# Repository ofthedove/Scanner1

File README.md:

# Scanner1
Simple LED scanner with two buttons controlled by an ATmega32U4

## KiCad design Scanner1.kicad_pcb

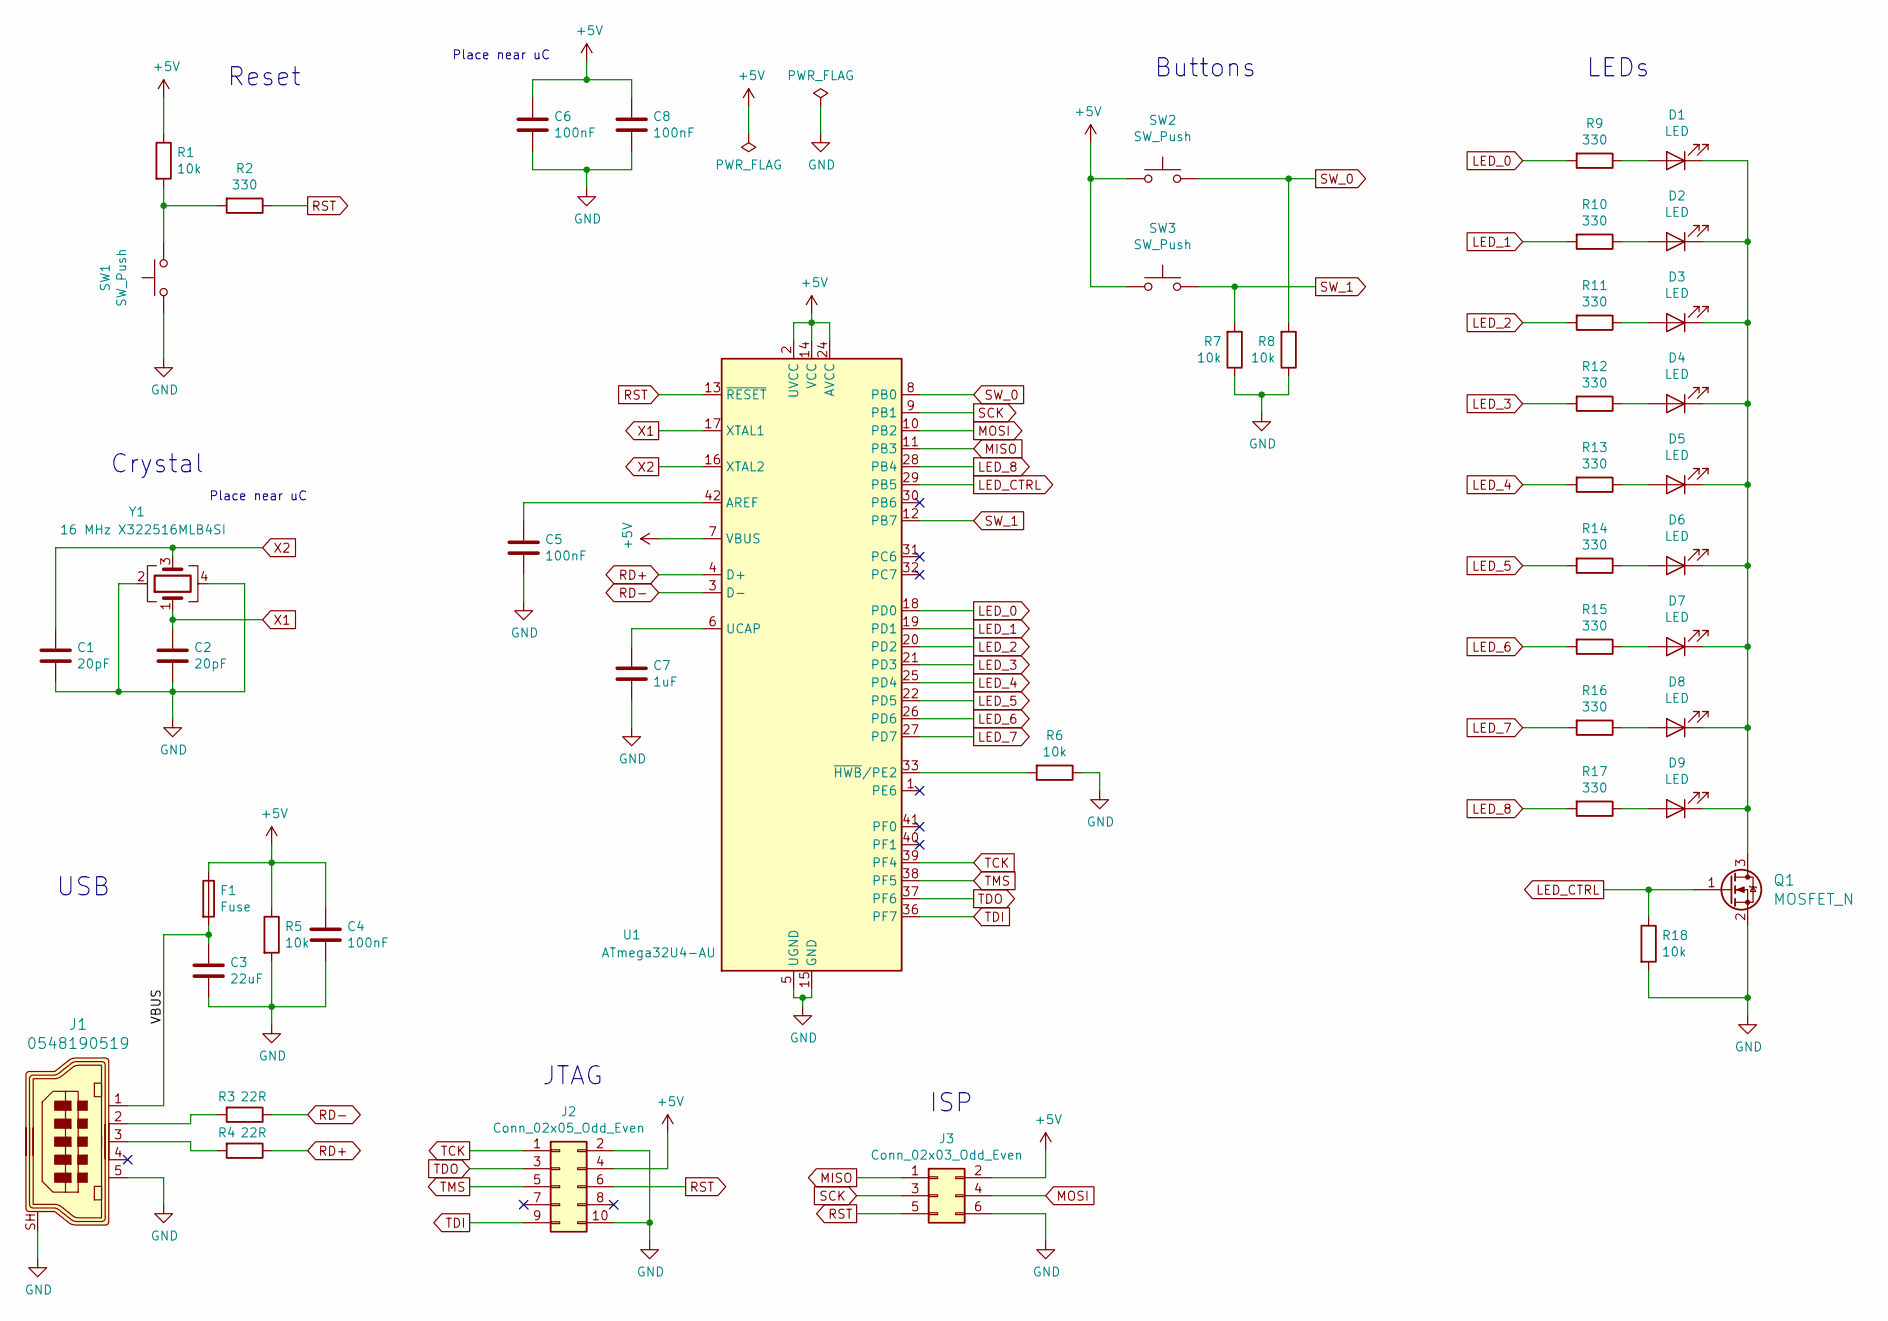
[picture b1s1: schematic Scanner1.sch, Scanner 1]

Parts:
C1, C2: 20pF; C_0805_2012Metric; LCSC Part # C1798
C3: 22uF; C_0805_2012Metric; LCSC Part # C45783
C4, C5, C6, C8: 100nF; C_0805_2012Metric; LCSC Part # C49678
C7: 1uF; C_0805_2012Metric; LCSC Part # C28323
D1, D2, D3, D4, D5, D6, D7, D8, D9: LED; LED_0805_2012Metric; LCSC Part # C2293
F1: Fuse; Fuse_0805_2012Metric; LCSC Part # C116170
J1: 0548190519; USB_Mini_B_Female_548190519; MPN 0548190519; Digi-Key_PN WM17115-ND
J2: Conn_02x05_Odd_Even; PinHeader_2x05_P2.54mm_Vertical
J3: Conn_02x03_Odd_Even; PinHeader_2x03_P2.54mm_Vertical
Q1: MOSFET_N; SOT-23; LCSC Part # C20917
R1, R5, R6, R7, R8, R18: 10k; R_0805_2012Metric; LCSC Part # C17414
R2, R9, R10, R11, R12, R13, R14, R15, R16, R17: 330; R_0805_2012Metric; LCSC Part # C17630
R3, R4: 22R; R_0805_2012Metric; LCSC Part # C17561
SW1, SW2, SW3: SW_Push; SW_PUSH_6mm_H7.3mm
U1: ATmega32U4-AU; TQFP-44_10x10mm_P0.8mm; LCSC Part # C44854
Y1: 16 MHz X322516MLB4SI; Crystal_SMD_3225-4Pin_3.2x2.5mm; LCSC Part # C13738

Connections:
+5V: C4.1, C6.1, C8.1, F1.1, J2.4, J3.2, R1.1, R5.1, SW2.2, SW3.2, U1.2 (UVCC), U1.7 (VBUS), U1.14 (VCC), U1.24 (AVCC), U1.34 (VCC), U1.44 (AVCC)
/VBUS: C3.1, F1.2, J1.1
GND: C1.1, C2.1, C3.2, C4.2, C5.2, C6.2, C7.2, C8.2, J1.5, J1.SH, J2.2, J2.10, J3.6, Q1.2 (S), R5.2, R6.1, R7.1, R8.1, R18.2, SW1.2, U1.5 (UGND), U1.15 (GND), U1.23 (GND), U1.35 (GND), U1.43 (GND), Y1.2, Y1.4
LED_0: R9.2, U1.18 (PD0)
LED_1: R10.2, U1.19 (PD1)
LED_2: R11.2, U1.20 (PD2)
LED_3: R12.2, U1.21 (PD3)
LED_4: R13.2, U1.25 (PD4)
LED_5: R14.2, U1.22 (PD5)
LED_6: R15.2, U1.26 (PD6)
LED_7: R16.2, U1.27 (PD7)
LED_8: R17.2, U1.28 (PB4)
LED_CTRL: Q1.1 (G), R18.1, U1.29 (PB5)
MISO: J3.1, U1.11 (PB3)
MOSI: J3.4, U1.10 (PB2)
unnamed: C5.1, U1.42 (AREF)
unnamed: C7.1, U1.6 (UCAP)
unnamed: D1.1 (K), D2.1 (K), D3.1 (K), D4.1 (K), D5.1 (K), D6.1 (K), D7.1 (K), D8.1 (K), D9.1 (K), Q1.3 (D)
unnamed: D1.2 (A), R9.1
unnamed: D2.2 (A), R10.1
unnamed: D3.2 (A), R11.1
unnamed: D4.2 (A), R12.1
unnamed: D5.2 (A), R13.1
unnamed: D6.2 (A), R14.1
unnamed: D7.2 (A), R15.1
unnamed: D8.2 (A), R16.1
unnamed: D9.2 (A), R17.1
unnamed: J1.2, R3.2
unnamed: J1.3, R4.2
unnamed: R1.2, R2.2, SW1.1
unnamed: R6.2, U1.33 (~HWB~/PE2)
RD+: R4.1, U1.4 (D+)
RD-: R3.1, U1.3 (D-)
RST: J2.6, J3.5, R2.1, U1.13 (~RESET)
SCK: J3.3, U1.9 (PB1)
SW_0: R8.2, SW2.1, U1.8 (PB0)
SW_1: R7.2, SW3.1, U1.12 (PB7)
TCK: J2.1, U1.39 (PF4)
TDI: J2.9, U1.36 (PF7)
TDO: J2.3, U1.37 (PF6)
TMS: J2.5, U1.38 (PF5)
X1: C2.2, U1.17 (XTAL1), Y1.1
X2: C1.2, U1.16 (XTAL2), Y1.3

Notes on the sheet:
ISP
JTAG
Reset
Crystal
USB
LEDs
Buttons
Place near uC

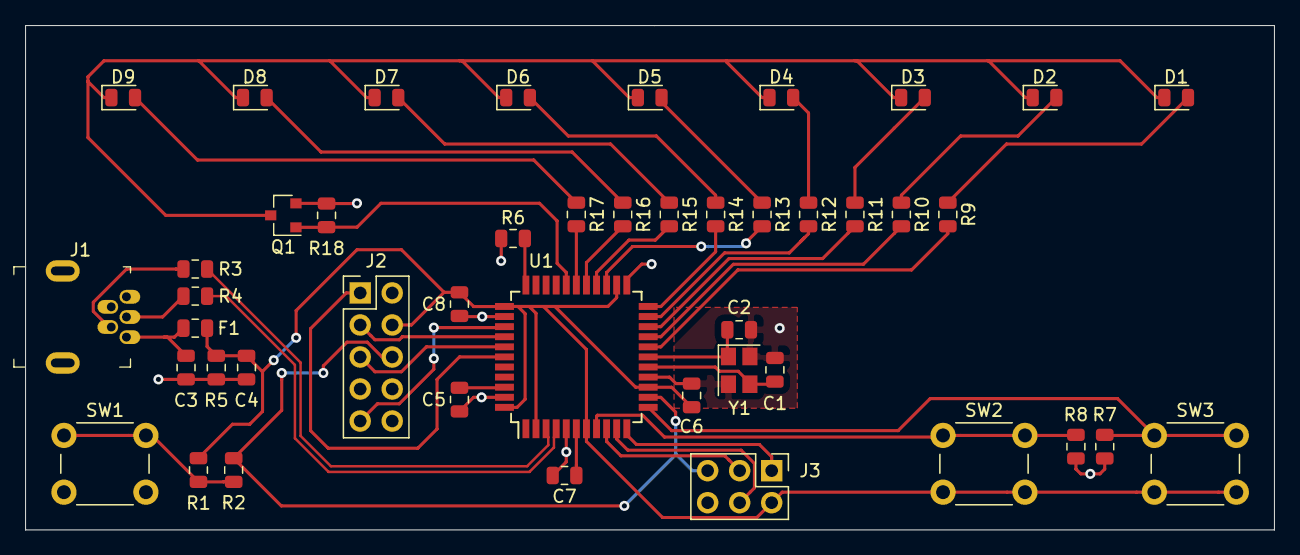
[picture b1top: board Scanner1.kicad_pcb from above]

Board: 2 copper layers, 99.1 x 40.0 mm, 45 parts (0 on the bottom side), 43 nets.

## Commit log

2020-08-29 Adding KiCad project. Schematic is basically complete, except for footprints and component specification
2020-08-29 Assign all footprints and JLCPCB part numbers. Generate BOM and netlist (netlist not included in repo)
2020-08-30 Fix issues with footprints vs symbols (some didn't line up, had to change some footprints and some symbols) and start layout
2020-08-30 More layout
2020-08-30 Layout and routing complete. Still needs silkscreen work and optionally extra pieces to cover the light bar
2020-08-30 Threw together fab files to get a quote. Looks like about 40 for 5, cheaper if I just have 2 of them assembled. Still need silkscreen, JLC part number, and holes (for JLC assembly and final mounting)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
